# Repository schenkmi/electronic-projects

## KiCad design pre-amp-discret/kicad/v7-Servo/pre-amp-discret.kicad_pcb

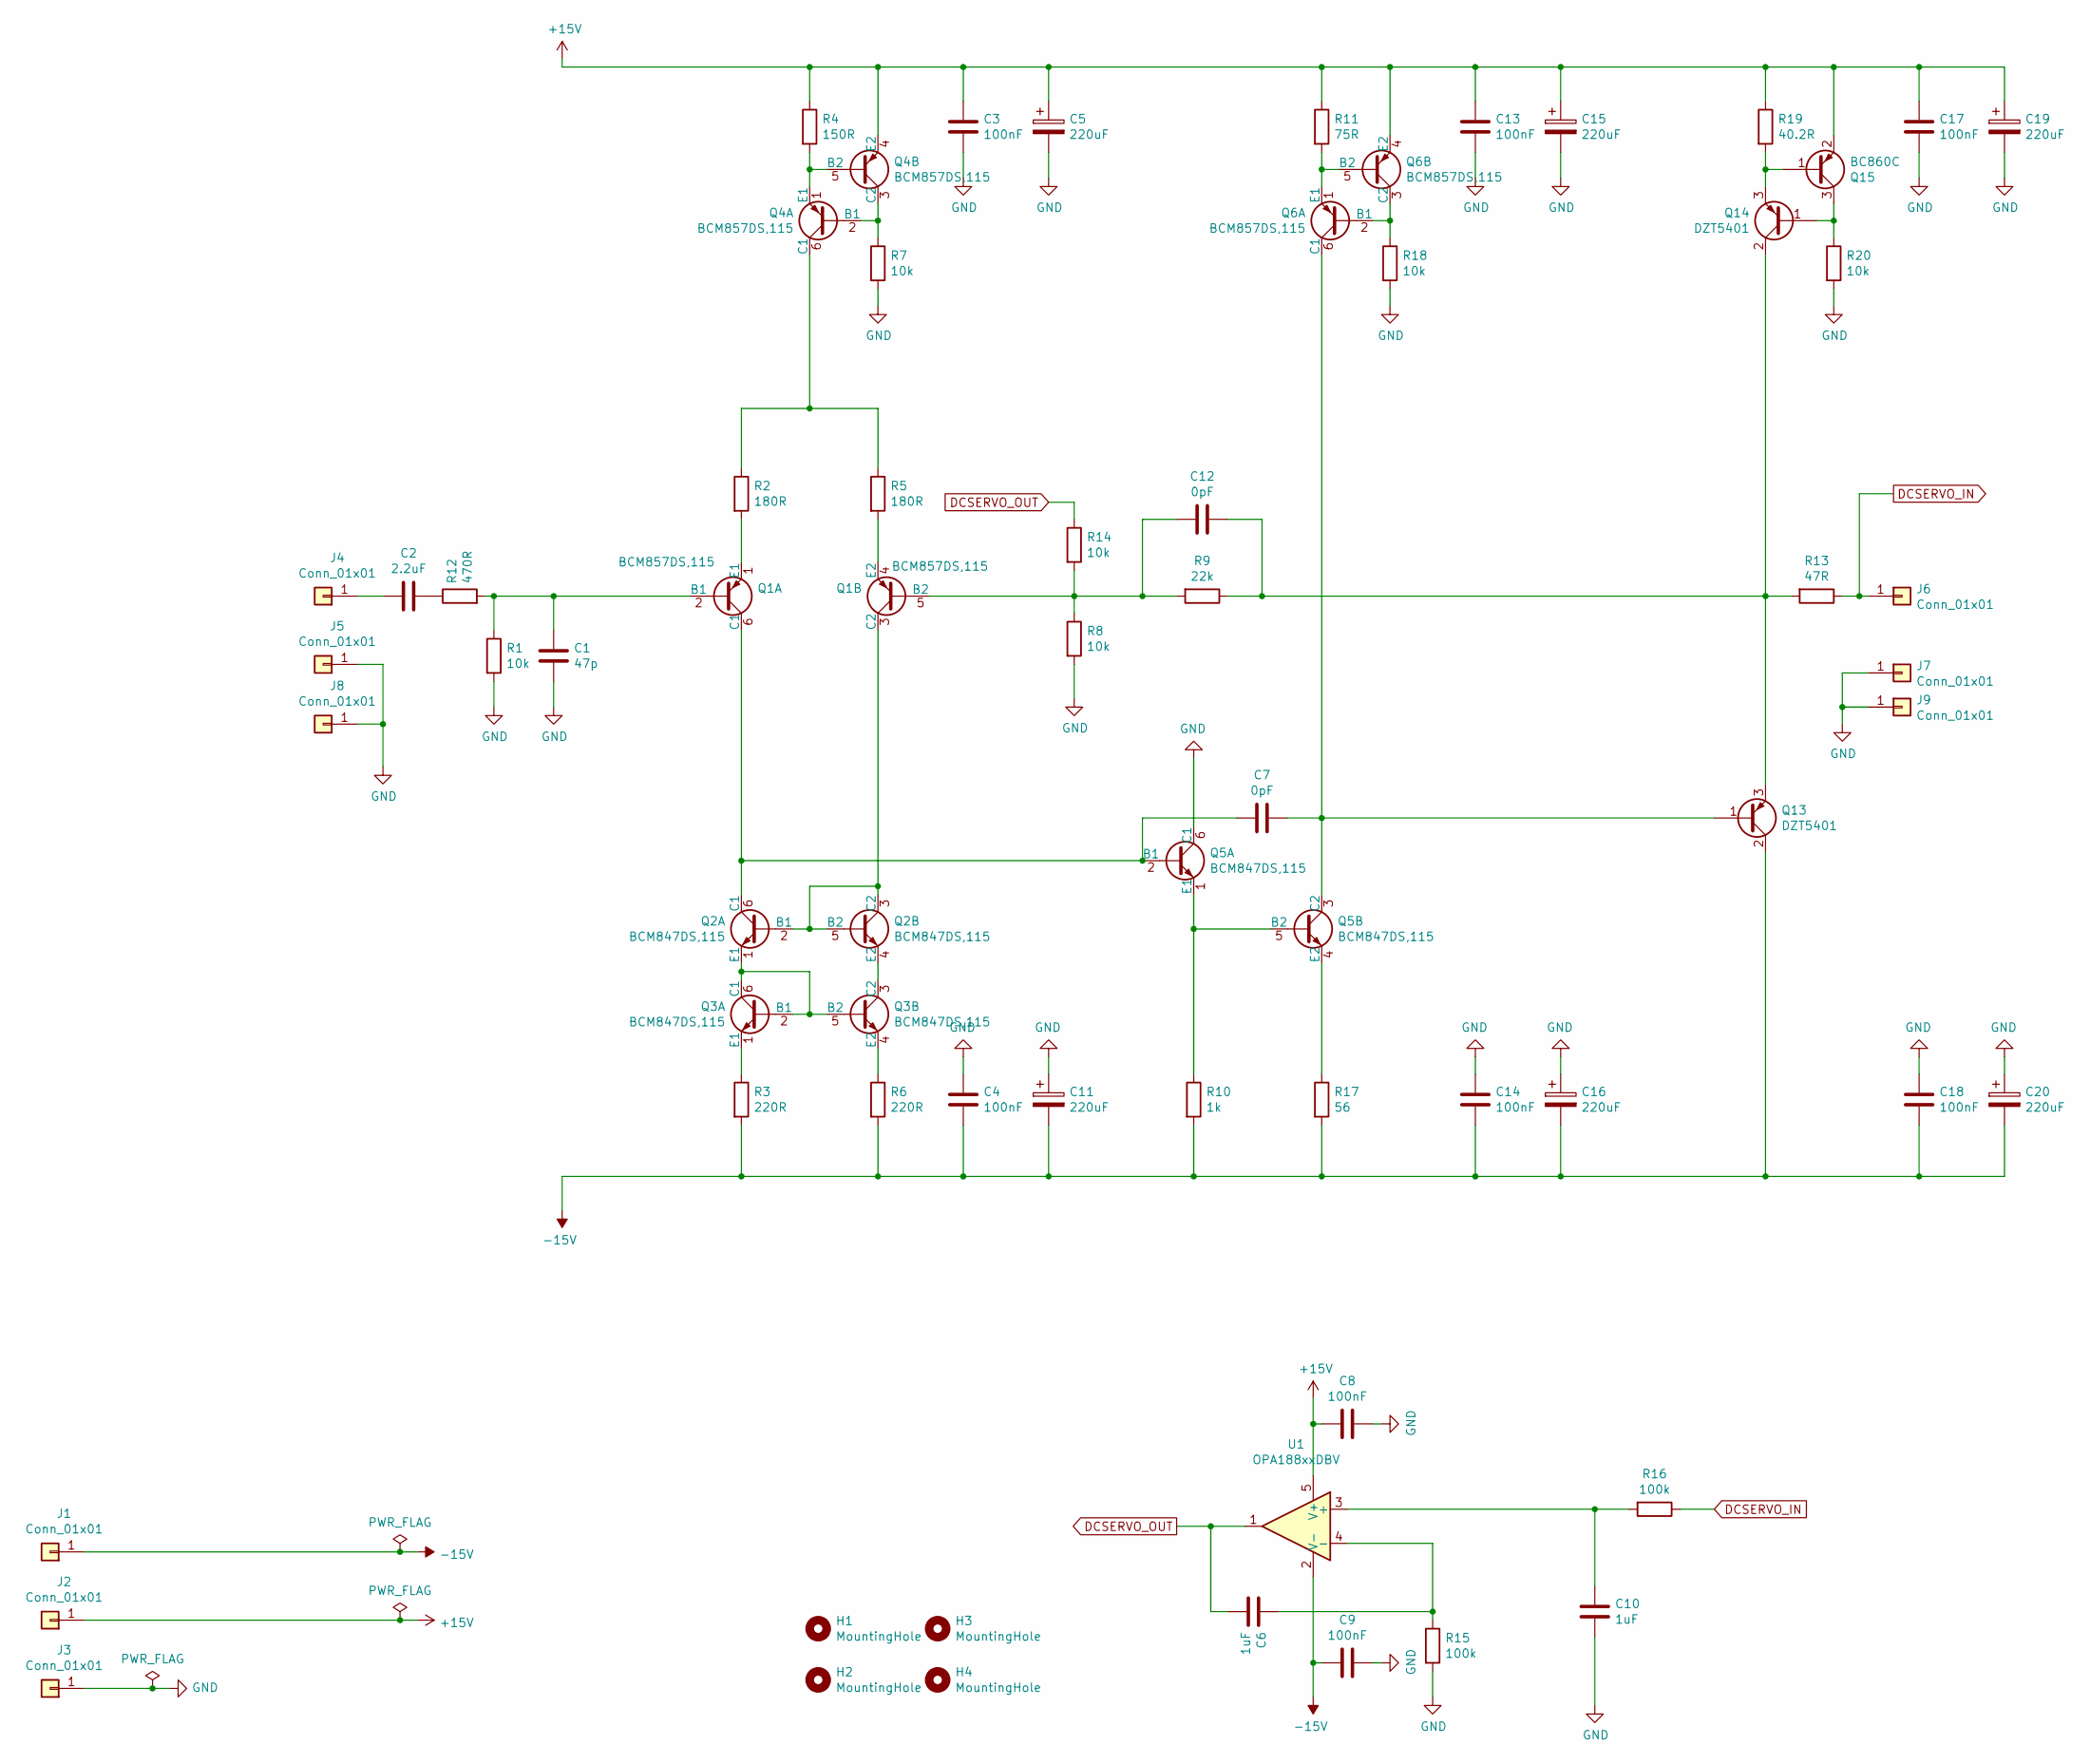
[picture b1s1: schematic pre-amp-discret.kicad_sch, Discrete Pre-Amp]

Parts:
C1: 47p; C_0805_2012Metric_Pad1.18x1.45mm_HandSolder
C2: 2.2uF; C_Rect_L7.2mm_W7.2mm_P5.00mm_FKS2_FKP2_MKS2_MKP2
C3, C4, C13, C14, C17, C18: 100nF; C_1210_3225Metric_Pad1.33x2.70mm_HandSolder
C5, C11, C15, C16, C19, C20: 220uF; CP_Radial_D8.0mm_P3.50mm
C6, C10: 1uF; C_1210_3225Metric_Pad1.33x2.70mm_HandSolder
C7, C12: 0pF; C_0805_2012Metric_Pad1.18x1.45mm_HandSolder
C8, C9: 100nF; C_0603_1608Metric_Pad1.08x0.95mm_HandSolder
H1, H2, H3, H4: MountingHole; MountingHole_3.2mm_M3
J1, J2, J3, J4, J5, J6, J7, J8, J9: Conn_01x01; Pin_D1.0mm_L10.0mm
Q1, Q4, Q6: BCM857DS,115; SC-74-6_1.5x2.9mm_P0.95mm
Q2, Q3, Q5: BCM847DS,115; SC-74-6_1.5x2.9mm_P0.95mm
Q13, Q14: DZT5401; SOT-223-3_TabPin2
Q15: BC860C; SOT-23
R1, R7, R8, R14, R18, R20: 10k; R_0805_2012Metric_Pad1.20x1.40mm_HandSolder
R2, R5: 180R; R_0805_2012Metric_Pad1.20x1.40mm_HandSolder
R3, R6: 220R; R_0805_2012Metric_Pad1.20x1.40mm_HandSolder
R4: 150R; R_0805_2012Metric_Pad1.20x1.40mm_HandSolder
R9: 22k; R_0805_2012Metric_Pad1.20x1.40mm_HandSolder
R10: 1k; R_0805_2012Metric_Pad1.20x1.40mm_HandSolder
R11: 75R; R_0805_2012Metric_Pad1.20x1.40mm_HandSolder
R12: 470R; R_0805_2012Metric_Pad1.20x1.40mm_HandSolder
R13: 47R; R_0805_2012Metric_Pad1.20x1.40mm_HandSolder
R15, R16: 100k; R_0805_2012Metric_Pad1.20x1.40mm_HandSolder
R17: 56; R_0805_2012Metric_Pad1.20x1.40mm_HandSolder
R19: 40.2R; R_0805_2012Metric_Pad1.20x1.40mm_HandSolder
U1: OPA188xxDBV; TSOT-23-5

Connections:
+15V: C3.2, C5.1, C8.2, C13.2, C15.1, C17.2, C19.1, J2.1, Q4.4 (E2), Q6.4 (E2), Q15.2 (E), R4.1, R11.1, R19.1, U1.5 (V+)
-15V: C4.1, C9.2, C11.2, C14.1, C16.2, C18.1, C20.2, J1.1, Q13.2 (C), R3.2, R6.2, R10.2, R17.2, U1.2 (V-)
DCSERVO_IN: J6.1, R13.1, R16.1
DCSERVO_OUT: C6.1, R14.1, U1.1
GND: C1.1, C3.1, C4.2, C5.2, C8.1, C9.1, C10.1, C11.1, C13.1, C14.2, C15.2, C16.1, C17.1, C18.2, C19.2, C20.1, J3.1, J5.1, J7.1, J8.1, J9.1, Q5.6 (C1), R1.2, R7.2, R8.2, R15.2, R18.2, R20.2
unnamed: C2.1, R12.1
unnamed: C2.2, J4.1
unnamed: C6.2, R15.1, U1.4 (-)
unnamed: C7.1, Q5.3 (C2), Q6.6 (C1), Q13.1 (B)
unnamed: C10.2, R16.2, U1.3 (+)
unnamed: C12.1, Q13.3 (E), Q14.2 (C), R9.1, R13.2
unnamed: C12.2, Q1.5 (B2), R8.1, R9.2, R14.2
unnamed: C1.2, Q1.2 (B1), R1.1, R12.2
unnamed: Q1.3 (C2), Q2.2 (B1), Q2.3 (C2), Q2.5 (B2)
unnamed: C7.2, Q1.6 (C1), Q2.6 (C1), Q5.2 (B1)
unnamed: Q2.1 (E1), Q3.2 (B1), Q3.5 (B2), Q3.6 (C1)
unnamed: Q2.4 (E2), Q3.3 (C2)
unnamed: Q14.1 (B), Q15.3 (C), R20.1
unnamed: Q14.3 (E), Q15.1 (B), R19.2
unnamed: Q4.6 (C1), R2.1, R5.1
unnamed: Q1.1 (E1), R2.2
unnamed: Q3.1 (E1), R3.1
unnamed: Q4.1 (E1), Q4.5 (B2), R4.2
unnamed: Q1.4 (E2), R5.2
unnamed: Q3.4 (E2), R6.1
unnamed: Q4.2 (B1), Q4.3 (C2), R7.1
unnamed: Q5.1 (E1), Q5.5 (B2), R10.1
unnamed: Q6.1 (E1), Q6.5 (B2), R11.2
unnamed: Q5.4 (E2), R17.1
unnamed: Q6.2 (B1), Q6.3 (C2), R18.1

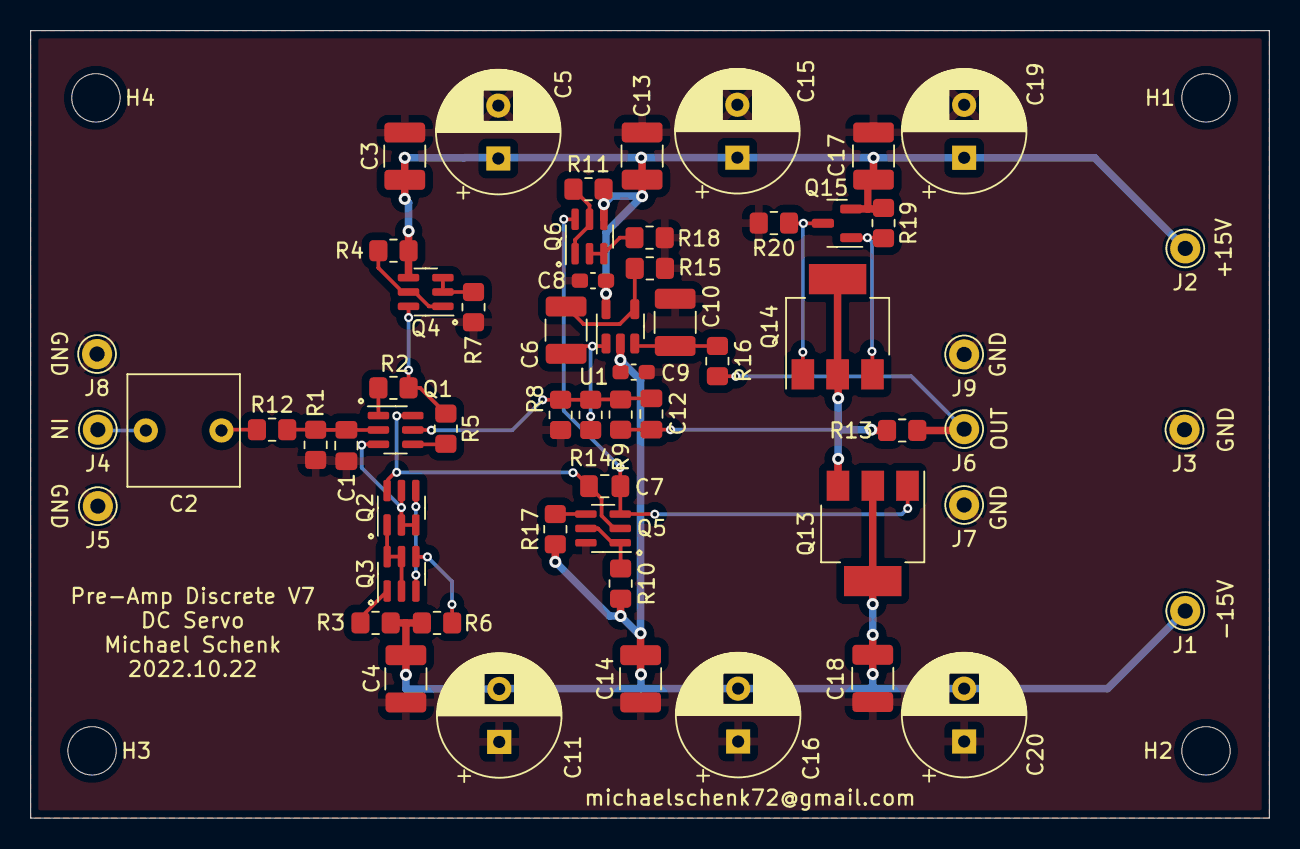
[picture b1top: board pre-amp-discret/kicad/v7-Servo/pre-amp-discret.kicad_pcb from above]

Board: 2 copper layers, 81.9 x 52.1 mm, 63 parts (0 on the bottom side), 30 nets.

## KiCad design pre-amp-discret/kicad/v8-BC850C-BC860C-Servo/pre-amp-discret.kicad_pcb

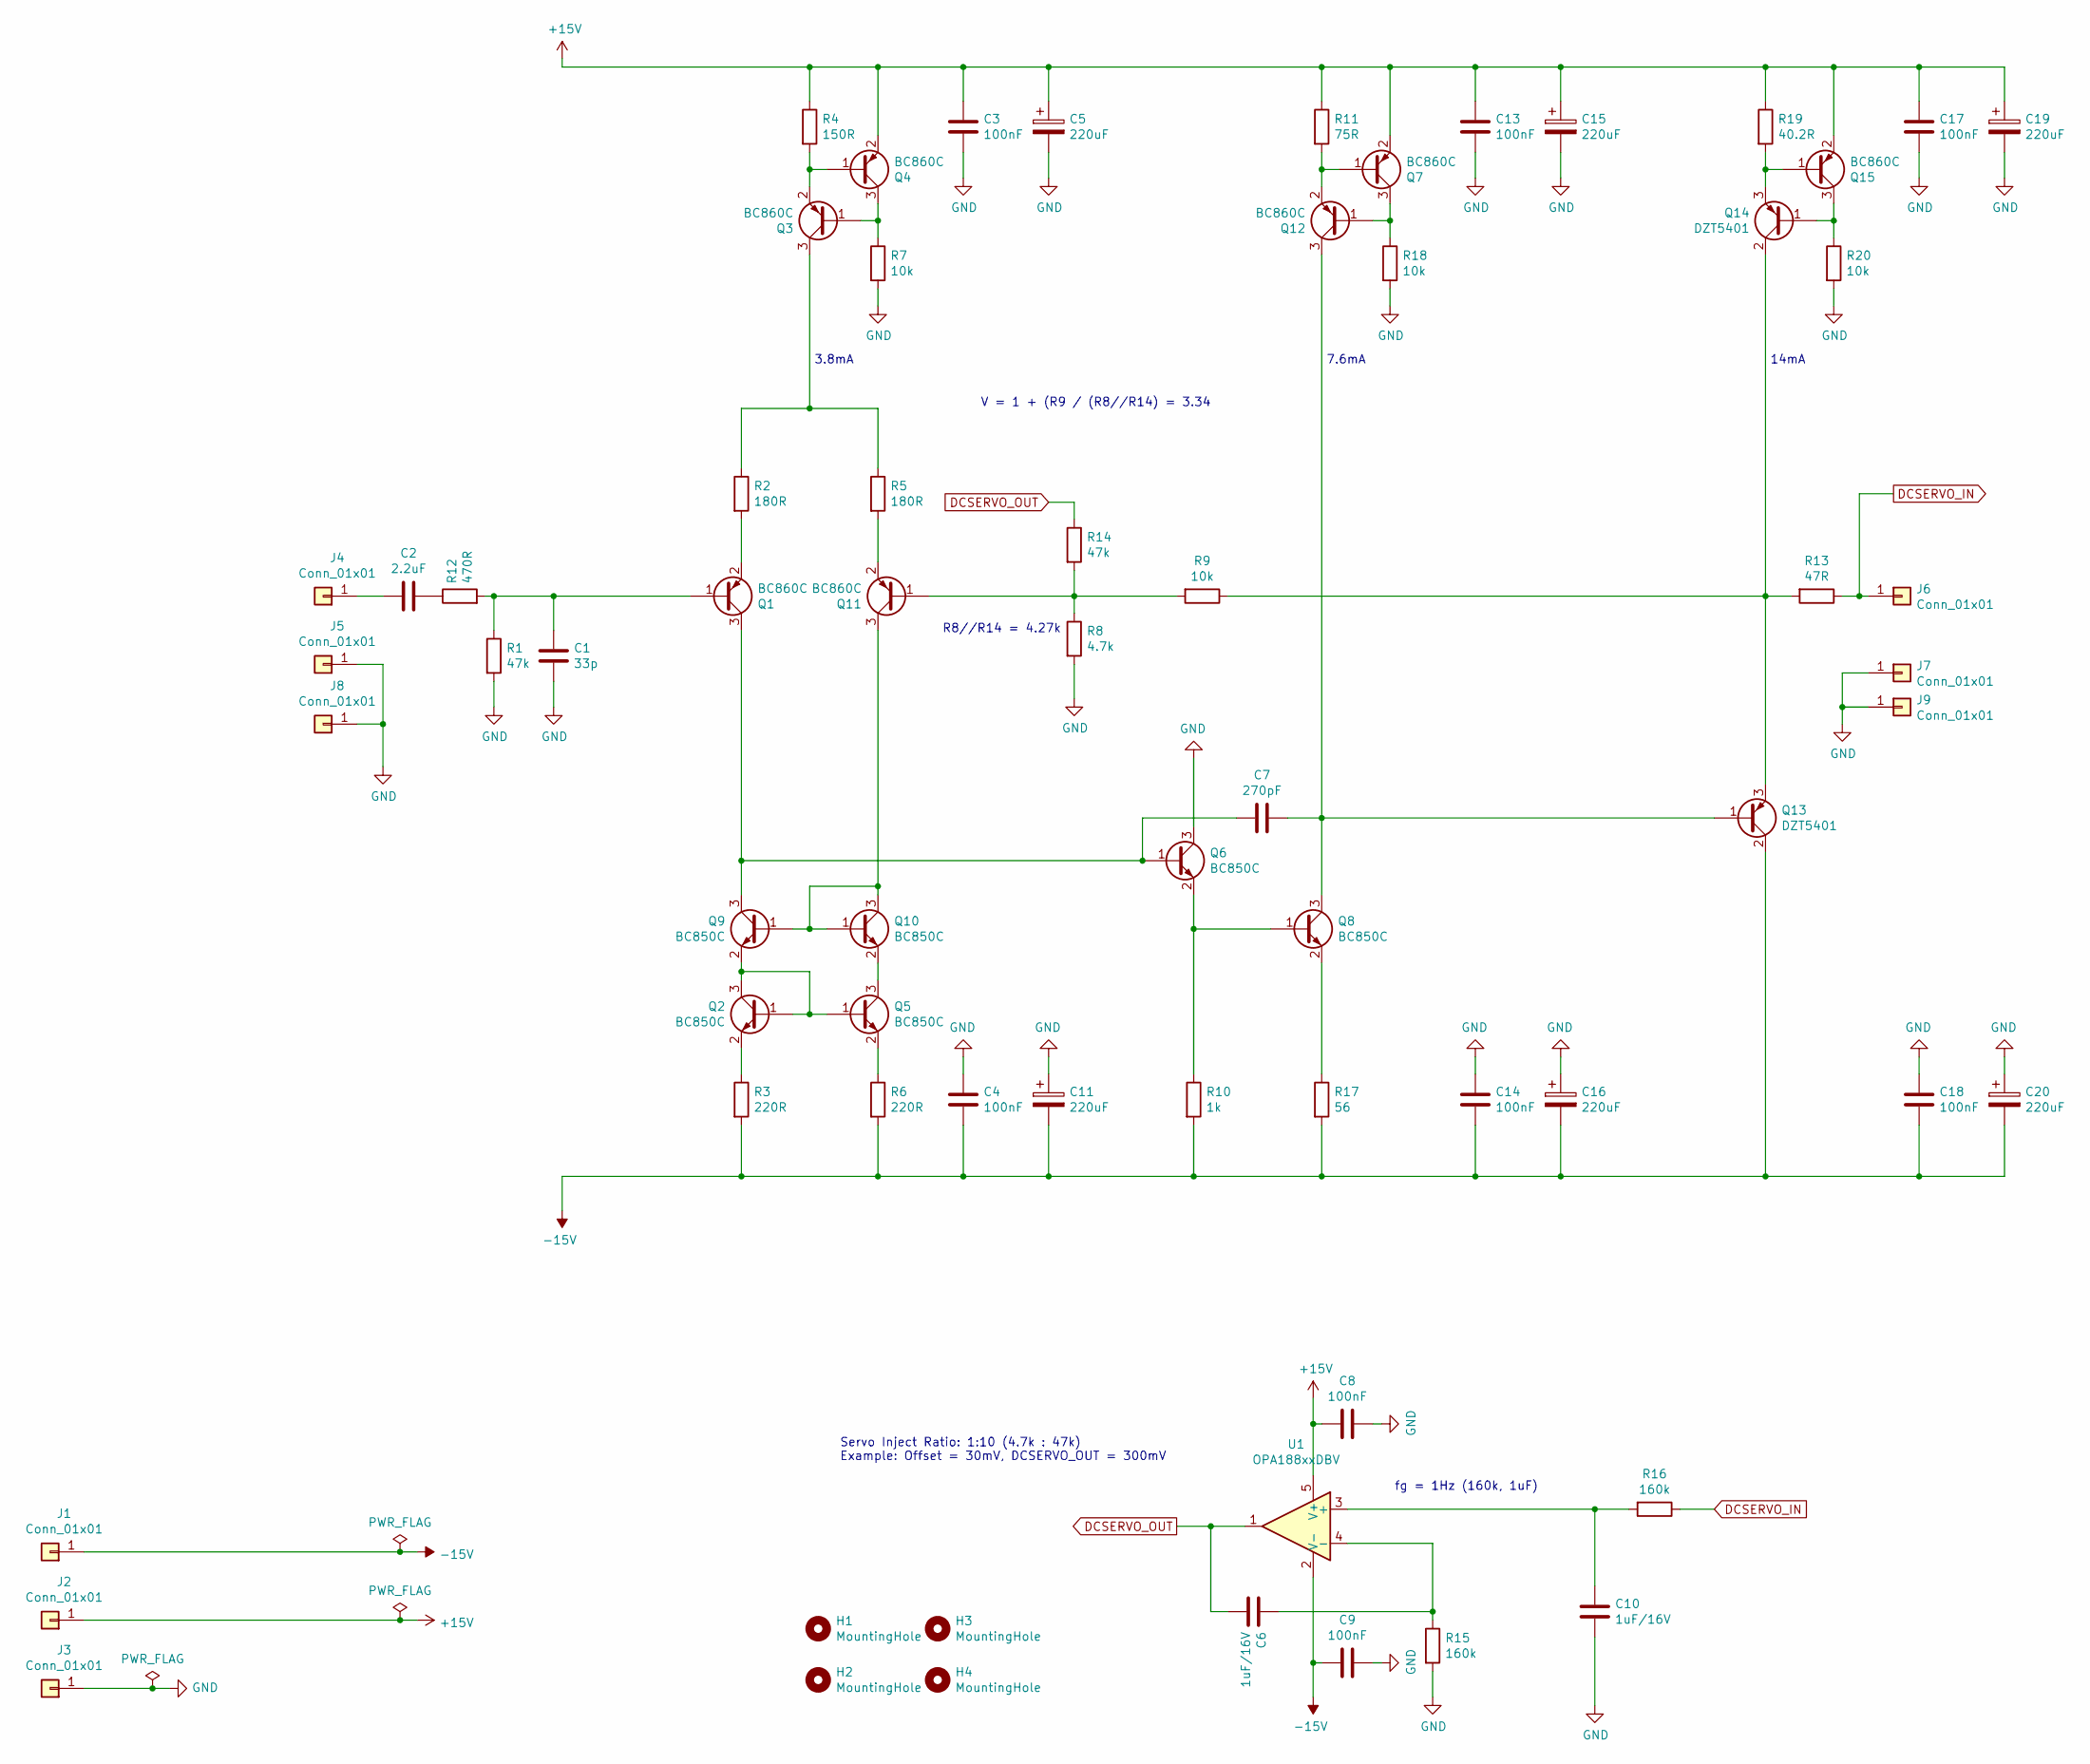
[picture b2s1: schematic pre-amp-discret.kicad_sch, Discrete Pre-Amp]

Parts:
C1: 33p; C_0805_2012Metric_Pad1.18x1.45mm_HandSolder
C2: 2.2uF; C_Rect_L7.2mm_W7.2mm_P5.00mm_FKS2_FKP2_MKS2_MKP2
C3, C4, C13, C14, C17, C18: 100nF; C_1210_3225Metric_Pad1.33x2.70mm_HandSolder
C5, C11, C15, C16, C19, C20: 220uF; CP_Radial_D8.0mm_P3.50mm
C6, C10: 1uF/16V; C_1210_3225Metric_Pad1.33x2.70mm_HandSolder
C7: 270pF; C_0805_2012Metric_Pad1.18x1.45mm_HandSolder
C8, C9: 100nF; C_0603_1608Metric_Pad1.08x0.95mm_HandSolder
H1, H2, H3, H4: MountingHole; MountingHole_3.2mm_M3
J1, J2, J3, J4, J5, J6, J7, J8, J9: Conn_01x01; Pin_D1.0mm_L10.0mm
Q1, Q3, Q4, Q7, Q11, Q12, Q15: BC860C; SOT-23
Q2, Q5, Q6, Q8, Q9, Q10: BC850C; SOT-23
Q13, Q14: DZT5401; SOT-223-3_TabPin2
R1, R14: 47k; R_0805_2012Metric_Pad1.20x1.40mm_HandSolder
R2, R5: 180R; R_0805_2012Metric_Pad1.20x1.40mm_HandSolder
R3, R6: 220R; R_0805_2012Metric_Pad1.20x1.40mm_HandSolder
R4: 150R; R_0805_2012Metric_Pad1.20x1.40mm_HandSolder
R7, R9, R18, R20: 10k; R_0805_2012Metric_Pad1.20x1.40mm_HandSolder
R8: 4.7k; R_0805_2012Metric_Pad1.20x1.40mm_HandSolder
R10: 1k; R_0805_2012Metric_Pad1.20x1.40mm_HandSolder
R11: 75R; R_0805_2012Metric_Pad1.20x1.40mm_HandSolder
R12: 470R; R_0805_2012Metric_Pad1.20x1.40mm_HandSolder
R13: 47R; R_0805_2012Metric_Pad1.20x1.40mm_HandSolder
R15, R16: 160k; R_0805_2012Metric_Pad1.20x1.40mm_HandSolder
R17: 56; R_0805_2012Metric_Pad1.20x1.40mm_HandSolder
R19: 40.2R; R_0805_2012Metric_Pad1.20x1.40mm_HandSolder
U1: OPA188xxDBV; TSOT-23-5

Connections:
+15V: C3.2, C5.1, C8.2, C13.2, C15.1, C17.2, C19.1, J2.1, Q4.2 (E), Q7.2 (E), Q15.2 (E), R4.1, R11.1, R19.1, U1.5 (V+)
-15V: C4.1, C9.2, C11.2, C14.1, C16.2, C18.1, C20.2, J1.1, Q13.2 (C), R3.2, R6.2, R10.2, R17.2, U1.2 (V-)
DCSERVO_IN: J6.1, R13.1, R16.1
DCSERVO_OUT: C6.1, R14.1, U1.1
GND: C1.1, C3.1, C4.2, C5.2, C8.1, C9.1, C10.1, C11.1, C13.1, C14.2, C15.2, C16.1, C17.1, C18.2, C19.2, C20.1, J3.1, J5.1, J7.1, J8.1, J9.1, Q6.3 (C), R1.2, R7.2, R8.2, R15.2, R18.2, R20.2
unnamed: C1.2, Q1.1 (B), R1.1, R12.2
unnamed: C2.1, R12.1
unnamed: C2.2, J4.1
unnamed: C6.2, R15.1, U1.4 (-)
unnamed: C7.1, Q8.3 (C), Q12.3 (C), Q13.1 (B)
unnamed: C7.2, Q1.3 (C), Q6.1 (B), Q9.3 (C)
unnamed: C10.2, R16.2, U1.3 (+)
unnamed: Q1.2 (E), R2.2
unnamed: Q2.1 (B), Q2.3 (C), Q5.1 (B), Q9.2 (E)
unnamed: Q2.2 (E), R3.1
unnamed: Q3.1 (B), Q4.3 (C), R7.1
unnamed: Q3.2 (E), Q4.1 (B), R4.2
unnamed: Q3.3 (C), R2.1, R5.1
unnamed: Q5.2 (E), R6.1
unnamed: Q6.2 (E), Q8.1 (B), R10.1
unnamed: Q8.2 (E), R17.1
unnamed: Q9.1 (B), Q10.1 (B), Q10.3 (C), Q11.3 (C)
unnamed: Q5.3 (C), Q10.2 (E)
unnamed: Q11.1 (B), R8.1, R9.2, R14.2
unnamed: Q11.2 (E), R5.2
unnamed: Q7.3 (C), Q12.1 (B), R18.1
unnamed: Q7.1 (B), Q12.2 (E), R11.2
unnamed: Q13.3 (E), Q14.2 (C), R9.1, R13.2
unnamed: Q14.1 (B), Q15.3 (C), R20.1
unnamed: Q14.3 (E), Q15.1 (B), R19.2

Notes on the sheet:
fg = 1Hz (160k, 1uF)
R8//R14 = 4.27k
14mA
3.8mA
V = 1 + (R9 / (R8//R14) = 3.34
Servo Inject Ratio: 1:10 (4.7k : 47k) Example: Offset = 30mV, DCSERVO_OUT = 300mV
7.6mA

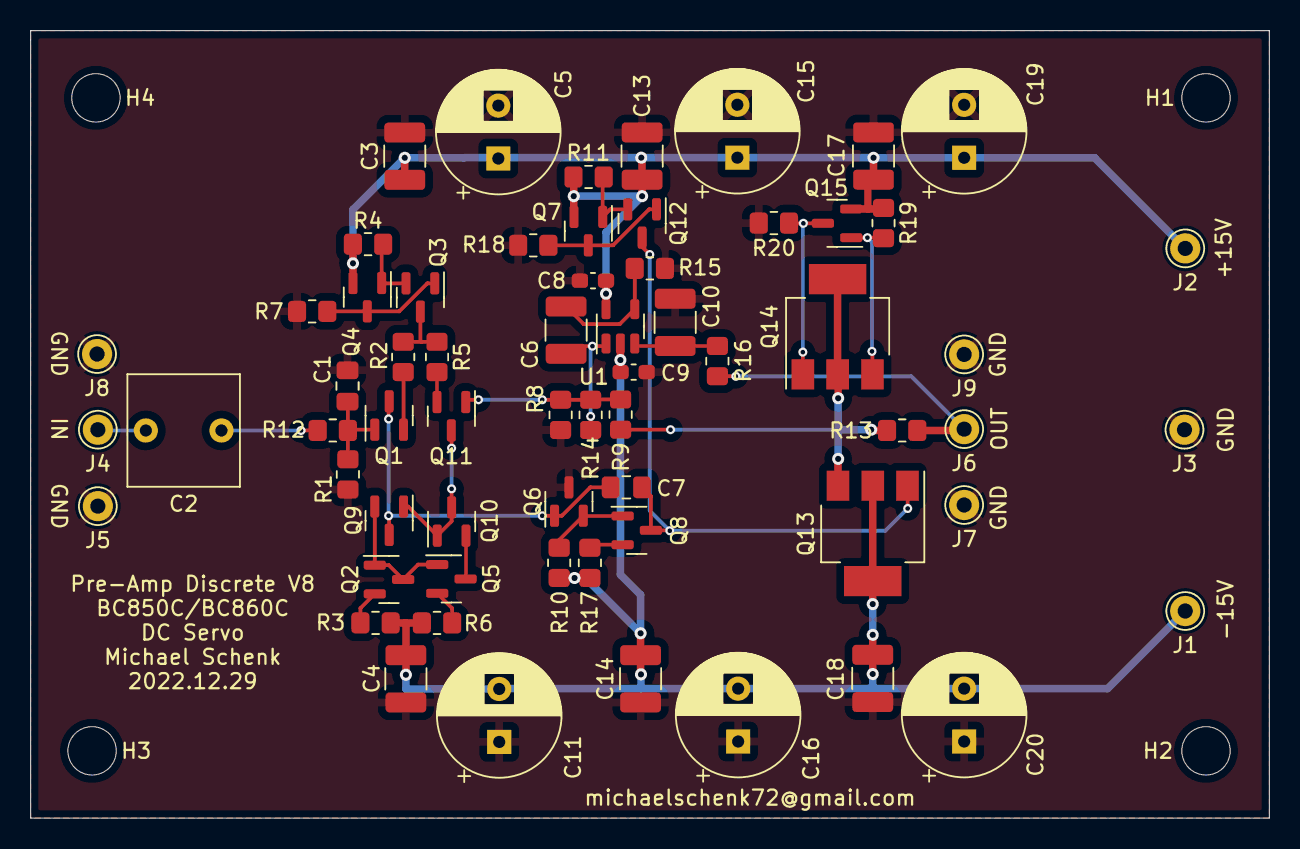
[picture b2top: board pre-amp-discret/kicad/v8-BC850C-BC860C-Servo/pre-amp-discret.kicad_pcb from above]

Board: 2 copper layers, 81.9 x 52.1 mm, 68 parts (0 on the bottom side), 30 nets.

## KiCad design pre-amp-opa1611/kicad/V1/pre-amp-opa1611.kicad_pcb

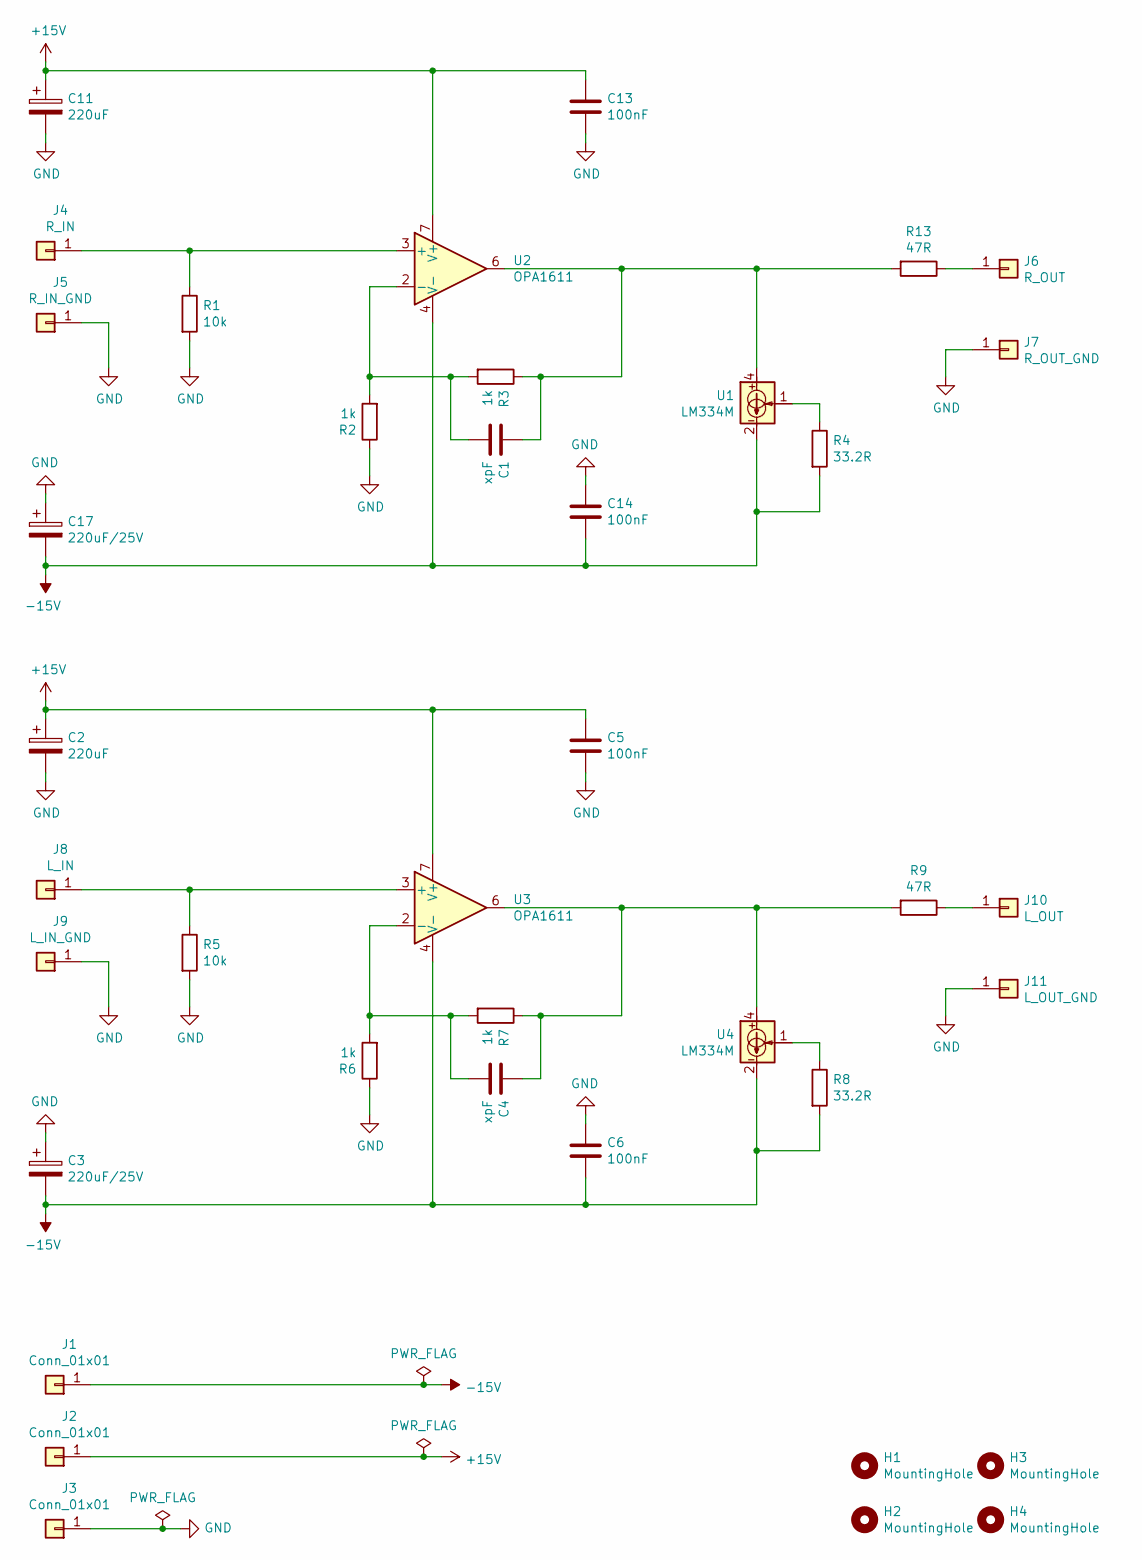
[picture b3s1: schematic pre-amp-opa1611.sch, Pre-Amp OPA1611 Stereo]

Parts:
C1, C4: xpF; C_0805_2012Metric_Pad1.18x1.45mm_HandSolder
C2, C11: 220uF; CP_Radial_D8.0mm_P3.50mm
C3, C17: 220uF/25V; CP_Radial_D8.0mm_P3.50mm
C5, C6, C13, C14: 100nF; C_1210_3225Metric_Pad1.33x2.70mm_HandSolder
H1, H2, H3, H4: MountingHole; MountingHole_3.2mm_M3
J1, J2, J3: Conn_01x01; Pin_D1.0mm_L10.0mm
J4: R_IN; Pin_D1.0mm_L10.0mm
J5: R_IN_GND; Pin_D1.0mm_L10.0mm
J6: R_OUT; Pin_D1.0mm_L10.0mm
J7: R_OUT_GND; Pin_D1.0mm_L10.0mm
J8: L_IN; Pin_D1.0mm_L10.0mm
J9: L_IN_GND; Pin_D1.0mm_L10.0mm
J10: L_OUT; Pin_D1.0mm_L10.0mm
J11: L_OUT_GND; Pin_D1.0mm_L10.0mm
R1, R5: 10k; R_0805_2012Metric_Pad1.20x1.40mm_HandSolder
R2, R3, R6, R7: 1k; R_0805_2012Metric_Pad1.20x1.40mm_HandSolder
R4, R8: 33.2R; R_0805_2012Metric_Pad1.20x1.40mm_HandSolder
R9, R13: 47R; R_0805_2012Metric_Pad1.20x1.40mm_HandSolder
U1, U4: LM334M; SOIC-8_3.9x4.9mm_P1.27mm
U2, U3: OPA1611; SOIC-8_3.9x4.9mm_P1.27mm

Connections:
+15V: C2.1, C5.2, C11.1, C13.2, J2.1, U2.7 (V+), U3.7 (V+)
-15V: C3.2, C6.1, C14.1, C17.2, J1.1, R4.2, R8.2, U1.2, U1.3, U1.6, U1.7, U2.4 (V-), U3.4 (V-), U4.2, U4.3, U4.6, U4.7
GND: C2.2, C3.1, C5.1, C6.2, C11.2, C13.1, C14.2, C17.1, J3.1, J5.1, J7.1, J9.1, J11.1, R1.2, R2.1, R5.2, R6.1
unnamed: C1.1, R2.2, R3.2, U2.2 (-)
unnamed: C1.2, R3.1, R13.2, U1.4, U2.6
unnamed: C4.1, R6.2, R7.2, U3.2 (-)
unnamed: C4.2, R7.1, R9.2, U3.6, U4.4
unnamed: J4.1, R1.1, U2.3 (+)
unnamed: J6.1, R13.1
unnamed: J8.1, R5.1, U3.3 (+)
unnamed: J10.1, R9.1
unnamed: R4.1, U1.1
unnamed: R8.1, U4.1

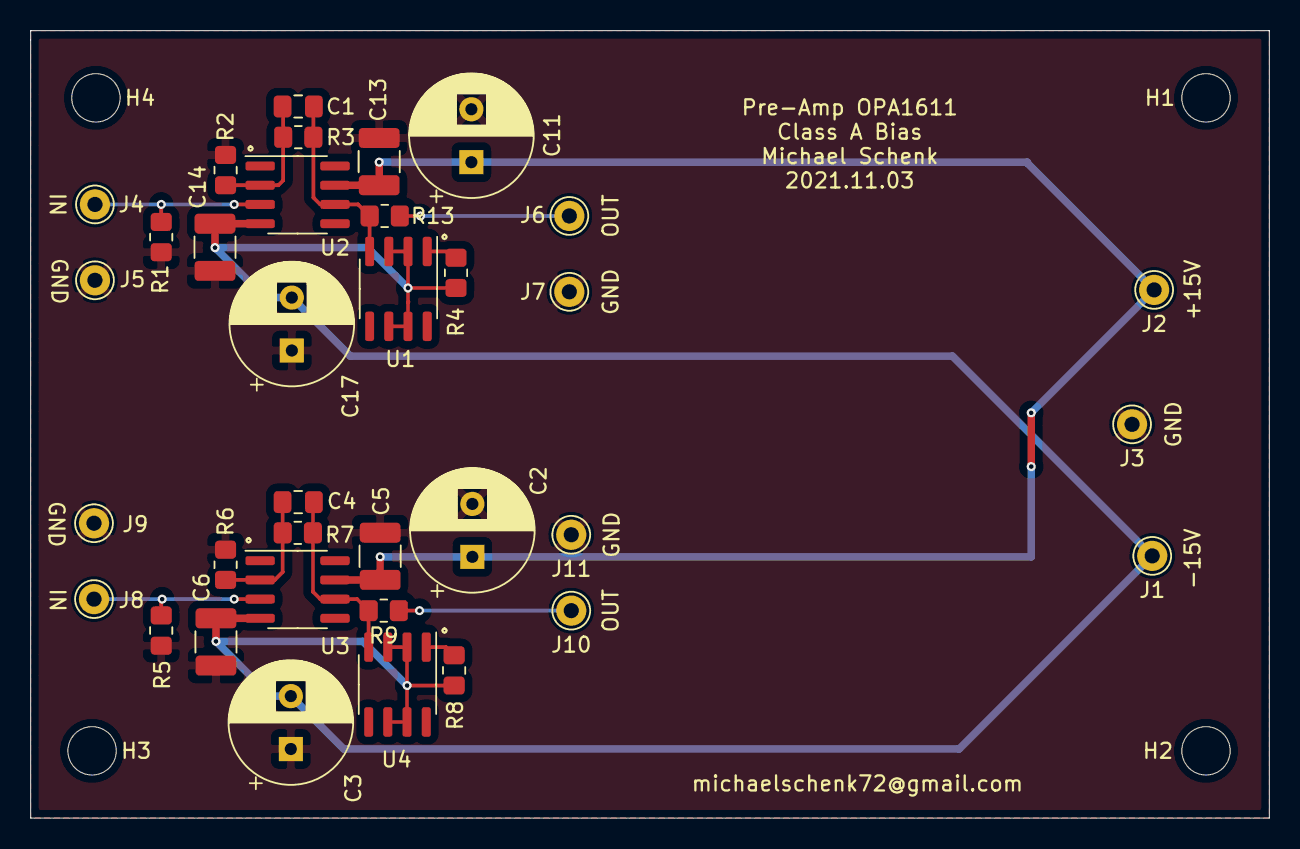
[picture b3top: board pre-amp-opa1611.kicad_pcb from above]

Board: 2 copper layers, 81.9 x 52.1 mm, 39 parts (0 on the bottom side), 13 nets.

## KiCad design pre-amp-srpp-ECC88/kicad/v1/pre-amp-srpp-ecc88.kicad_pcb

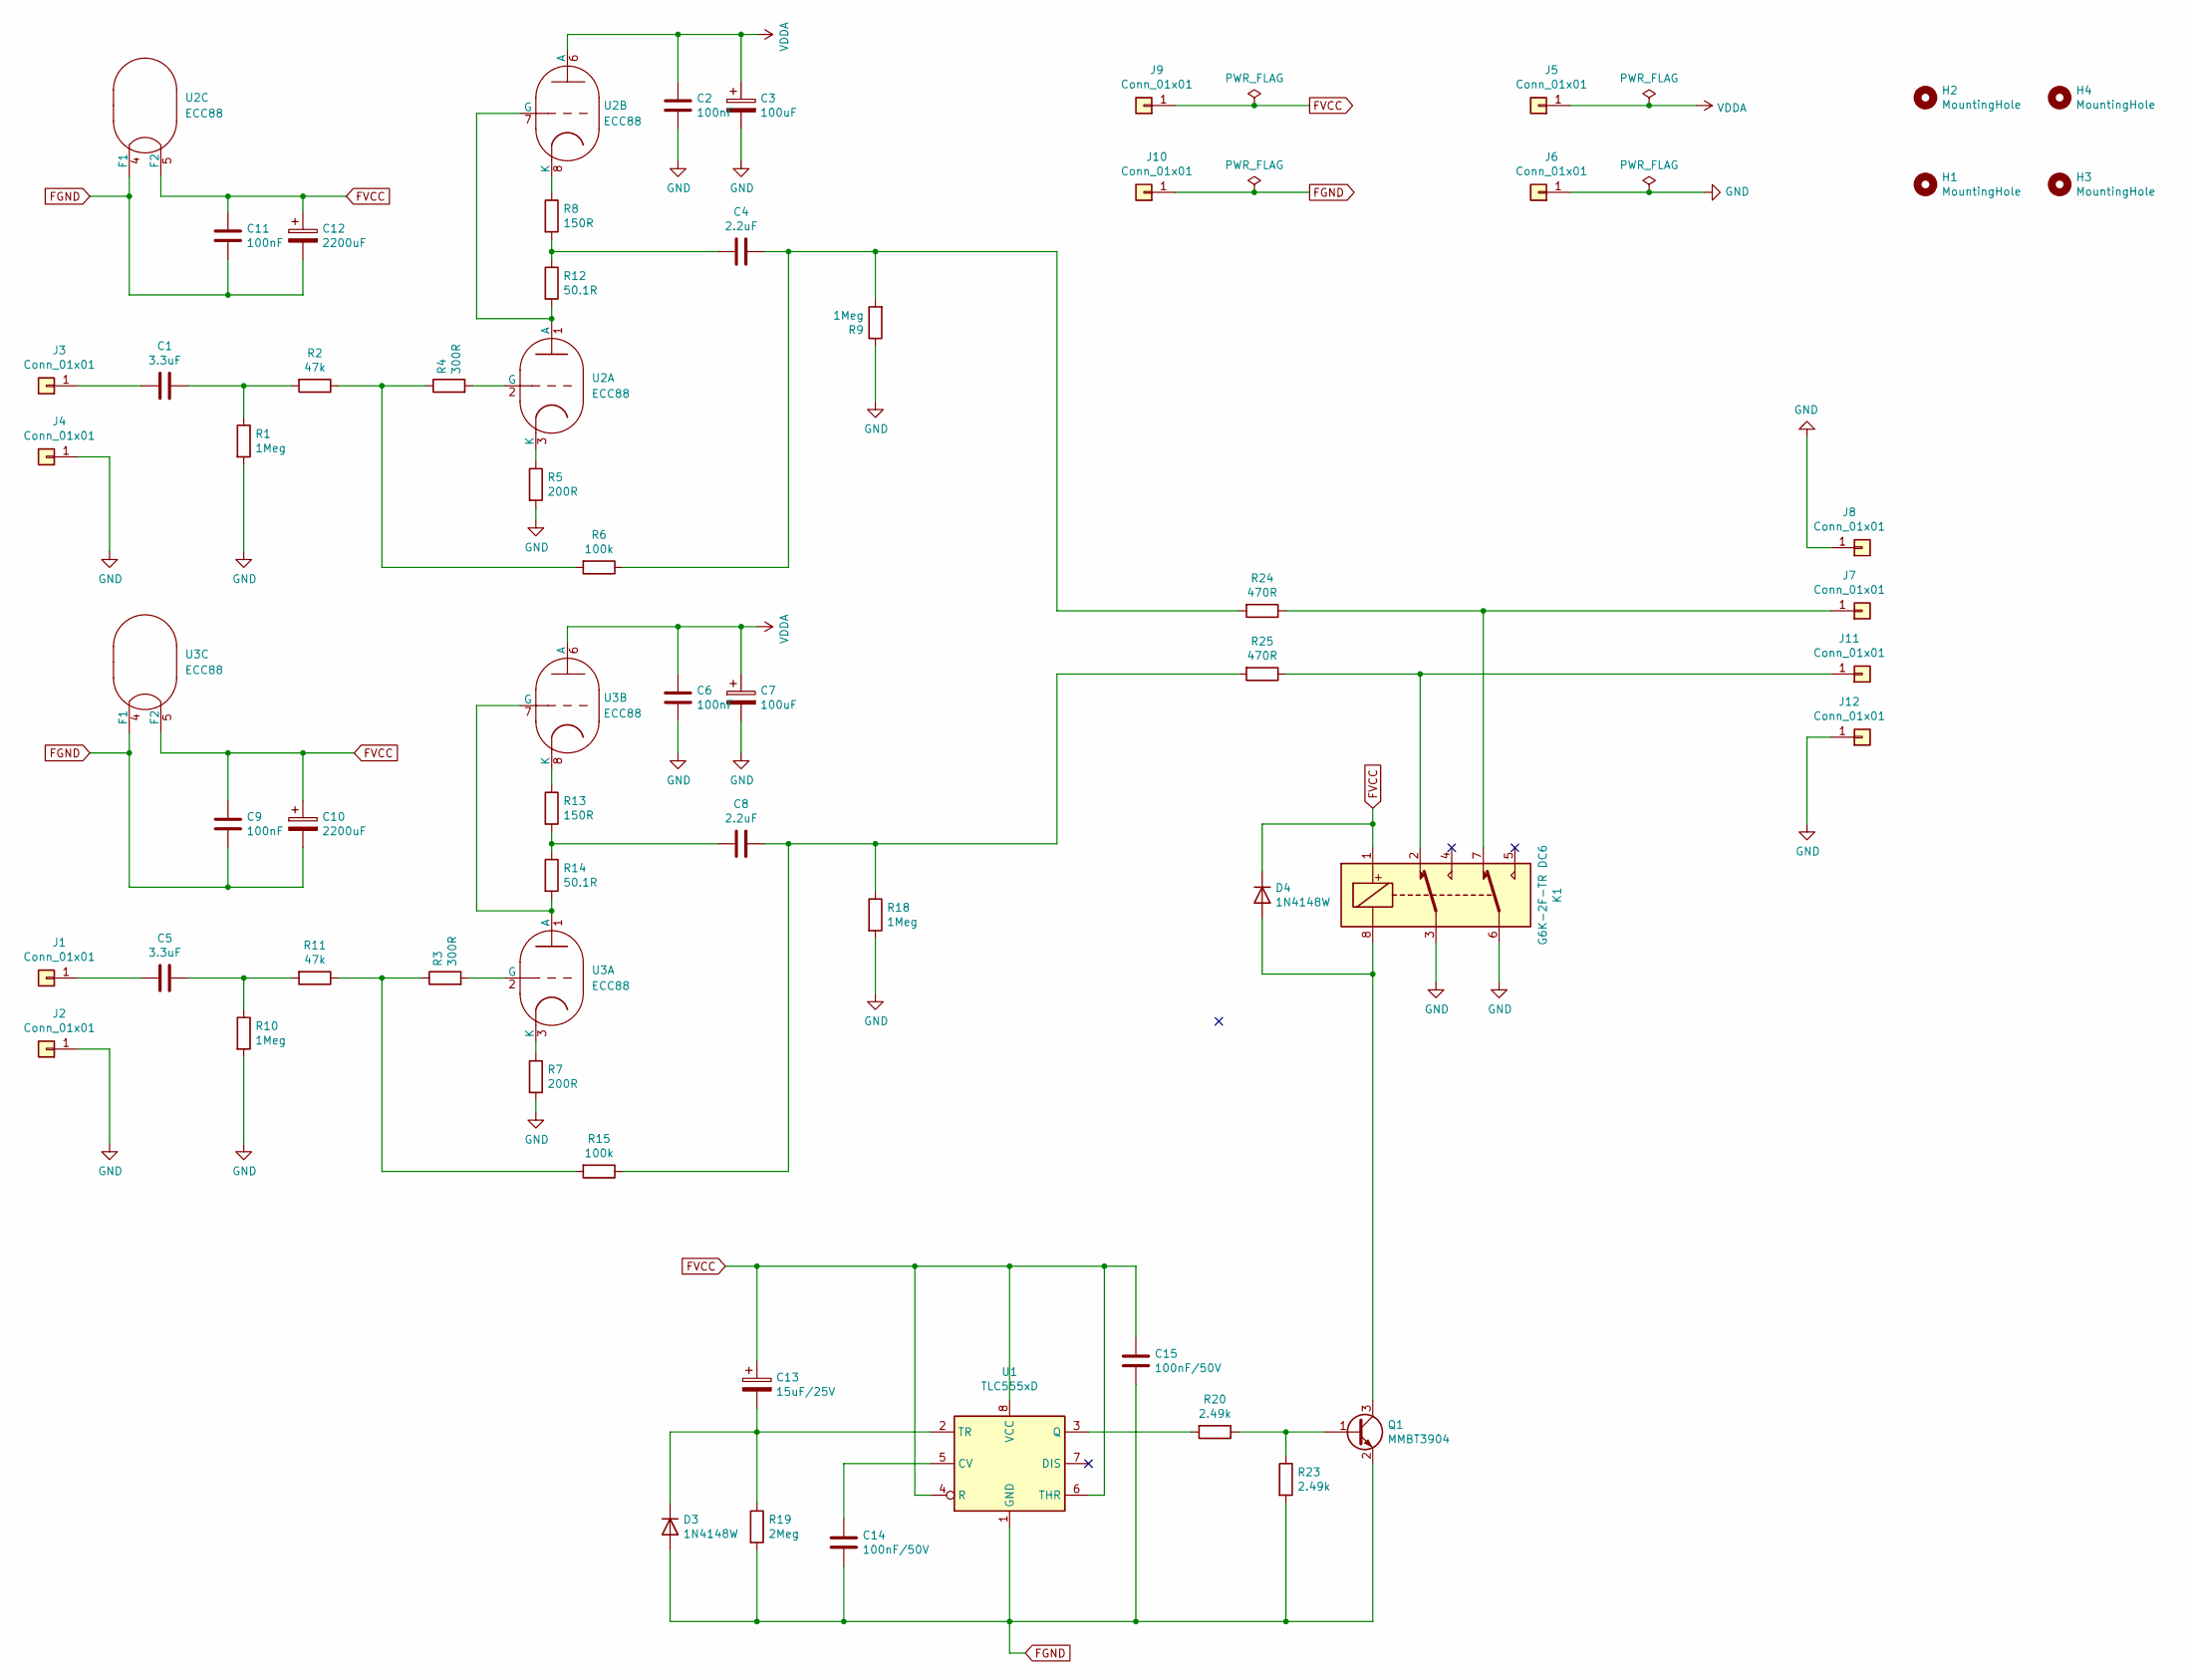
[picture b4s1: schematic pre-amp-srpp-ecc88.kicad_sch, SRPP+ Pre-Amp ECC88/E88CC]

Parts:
C1, C5: 3.3uF; C_Rect_L7.2mm_W7.2mm_P5.00mm_FKS2_FKP2_MKS2_MKP2
C2, C6: 100nF; C_Rect_L16.5mm_W5.0mm_P15.00mm_MKT
C3, C7: 100uF; CP_Radial_D18.0mm_P7.50mm
C4, C8: 2.2uF; C_Rect_L31.5mm_W11.0mm_P27.50mm_MKS4
C9, C11: 100nF; C_Rect_L7.2mm_W2.5mm_P5.00mm_FKS2_FKP2_MKS2_MKP2
C10, C12: 2200uF; CP_Radial_D16.0mm_P7.50mm
C13: 15uF/25V; CP_EIA-3216-12_Kemet-S_Pad1.58x1.35mm_HandSolder
C14, C15: 100nF/50V; C_0805_2012Metric_Pad1.18x1.45mm_HandSolder
D3, D4: 1N4148W; D_SOD-123
H1, H2, H3, H4: MountingHole; MountingHole_3.2mm_M3
J1, J2, J3, J4, J7, J8, J11, J12: Conn_01x01; Pin_D1.0mm_L10.0mm
J5, J6, J9, J10: Conn_01x01; Pin_D1.3mm_L11.0mm
K1: G6K-2F-TR DC6; Relay_DPDT_Omron_G6K-2F
Q1: MMBT3904; SOT-23
R1, R9, R10, R18: 1Meg; R_MELF_MMB-0207
R2, R11: 47k; R_MELF_MMB-0207
R3, R4: 300R; R_MELF_MMB-0207
R5, R7: 200R; R_MELF_MMB-0207
R6, R15: 100k; R_MELF_MMB-0207
R8, R13: 150R; R_MELF_MMB-0207
R12, R14: 50.1R; R_MELF_MMB-0207
R19: 2Meg; R_0805_2012Metric_Pad1.20x1.40mm_HandSolder
R20, R23: 2.49k; R_0805_2012Metric_Pad1.20x1.40mm_HandSolder
R24, R25: 470R; R_MELF_MMB-0207
U1: TLC555xD; SOIC-8_3.9x4.9mm_P1.27mm
U2, U3: ECC88; TubeNoval-ECC88

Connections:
FGND: C9.2, C10.2, C11.2, C12.2, C14.2, C15.2, D3.2 (A), J10.1, Q1.2 (E), R19.2, R23.2, U1.1 (GND), U2.4 (F1), U3.4 (F1)
FVCC: C9.1, C10.1, C11.1, C12.1, C13.1, C15.1, D4.1 (K), J9.1, K1.1, U1.4 (R), U1.6 (THR), U1.8 (VCC), U2.5 (F2), U3.5 (F2)
GND: C2.2, C3.2, C6.2, C7.2, J2.1, J4.1, J6.1, J8.1, J12.1, K1.3, K1.6, R1.2, R5.2, R7.2, R9.1, R10.2, R18.2
unnamed: C1.1, R1.1, R2.2
unnamed: C1.2, J3.1
unnamed: C4.1, R6.1, R9.2, R24.2
unnamed: C4.2, R8.2, R12.1
unnamed: C5.1, R10.1, R11.2
unnamed: C5.2, J1.1
unnamed: C8.1, R15.1, R18.1, R25.2
unnamed: C8.2, R13.2, R14.1
unnamed: C13.2, D3.1 (K), R19.1, U1.2 (TR)
unnamed: C14.1, U1.5 (CV)
unnamed: D4.2 (A), K1.8, Q1.3 (C)
unnamed: J7.1, K1.7, R24.1
unnamed: J11.1, K1.2, R25.1
unnamed: Q1.1 (B), R20.1, R23.1
unnamed: R2.1, R4.1, R6.2
unnamed: R3.2, U3.2 (G)
unnamed: R4.2, U2.2 (G)
unnamed: R5.1, U2.3 (K)
unnamed: R7.1, U3.3 (K)
unnamed: R8.1, U2.8 (K)
unnamed: R3.1, R11.1, R15.2
unnamed: R12.2, U2.1 (A), U2.7 (G)
unnamed: R13.1, U3.8 (K)
unnamed: R14.2, U3.1 (A), U3.7 (G)
unnamed: R20.2, U1.3 (Q)
VDDA: C2.1, C3.1, C6.1, C7.1, J5.1, U2.6 (A), U3.6 (A)
